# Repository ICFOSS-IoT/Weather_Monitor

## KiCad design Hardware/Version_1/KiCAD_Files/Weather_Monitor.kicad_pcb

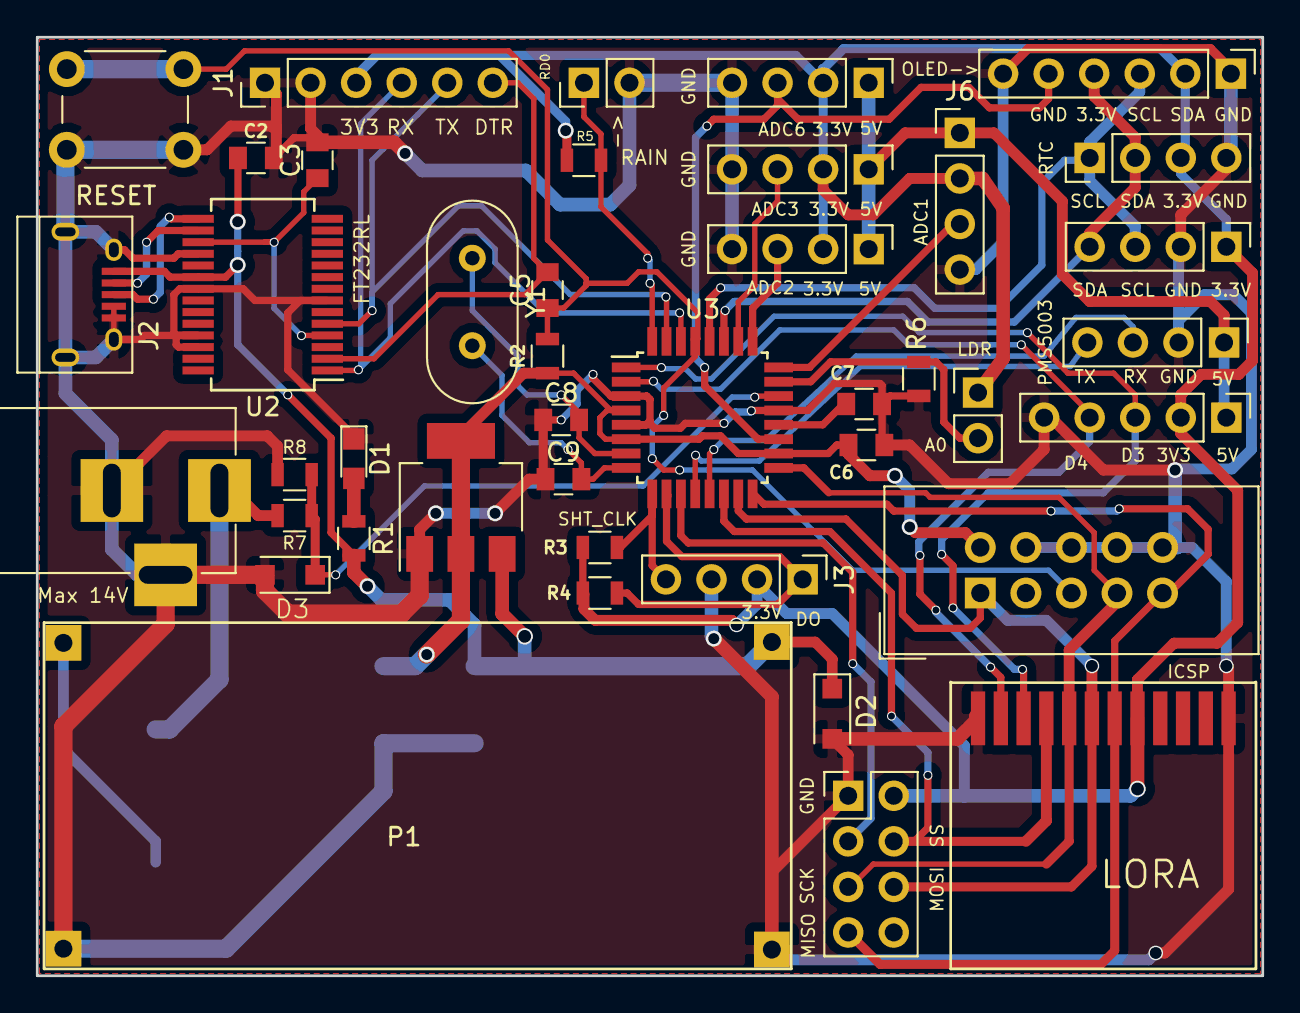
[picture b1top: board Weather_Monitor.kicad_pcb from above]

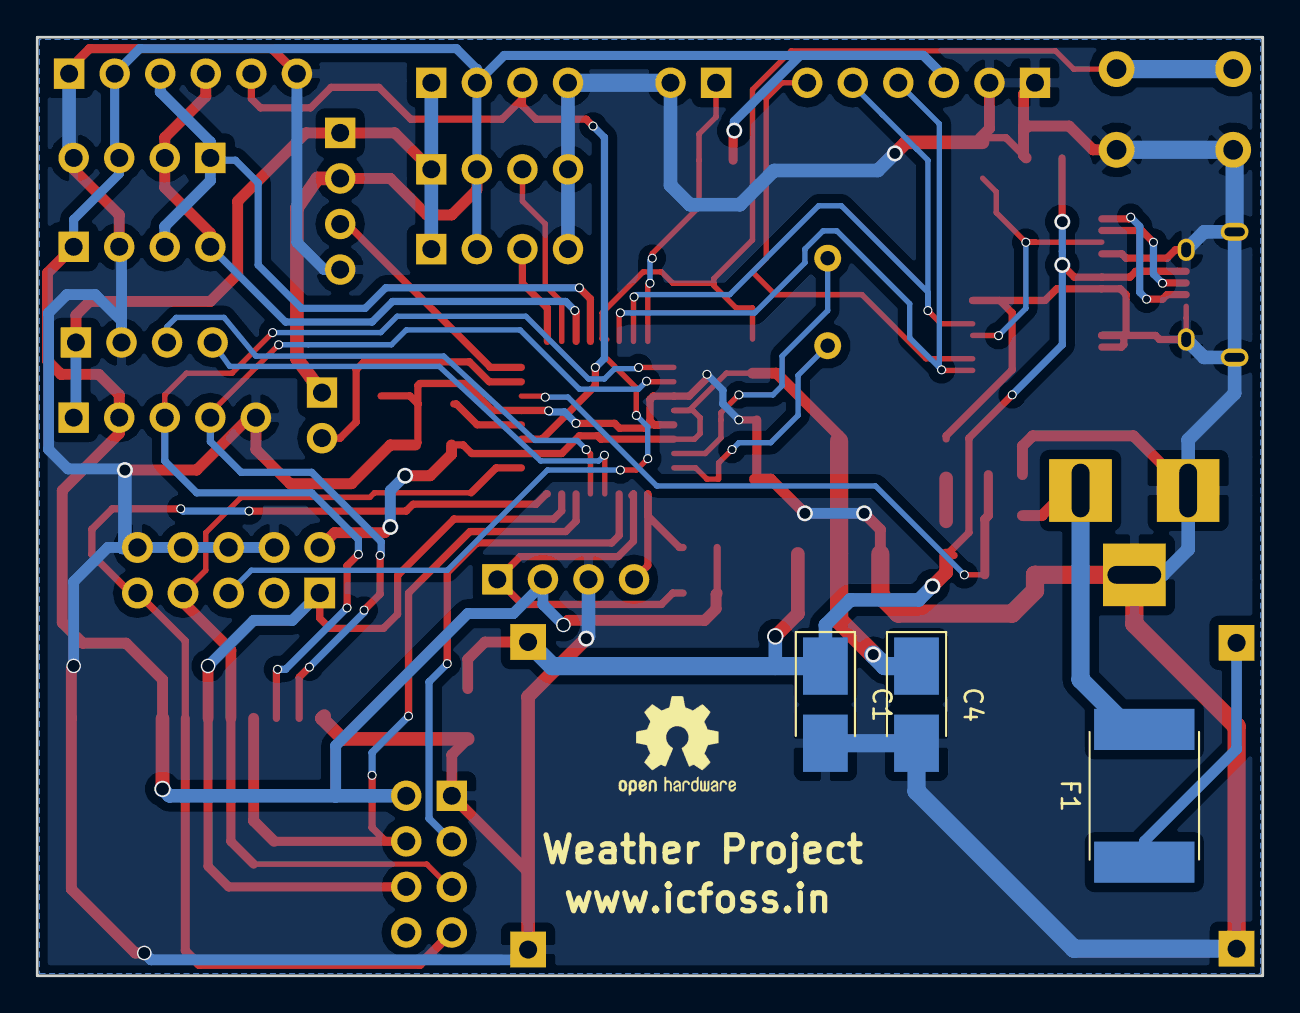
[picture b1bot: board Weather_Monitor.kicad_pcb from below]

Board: 2 copper layers, 68.3 x 52.3 mm, 45 parts (3 on the bottom side), 38 nets.

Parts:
C1, C4: 10uF; CP_Tantalum_Case-B_EIA-3528-21_Hand
C2, C3, C6, C7: 0.1uF; C_0805
C5: 0.1uf; C_0805
C8, C9: 22pF; C_0805
CON1: BARREL_JACK
CON2: AVR-ISP-10; IDC-Header_2x05_Pitch2.54mm_Straight
D1: LED; LED_0805
D2: 5.1V; D_SOD-123F
D3: 3.3V; D_SOD-123F
F1: Fuse; Fuse_SMD2920
J1: UART; Pin_Header_Straight_1x06_Pitch2.54mm
J2: MicroUSB; USB_Micro-B
J3: SHT11; Pin_Header_Straight_1x04_Pitch2.54mm
J4: RTC_DS3231; Pin_Header_Straight_1x04_Pitch2.54mm
J5: LoRa; XL_1278-SMT(SX1278)
J6: A1; Pin_Header_Straight_1x04_Pitch2.54mm
J7: A6; Pin_Header_Straight_1x04_Pitch2.54mm
J8: Rain_Sensor; Pin_Header_Straight_1x02_Pitch2.54mm
J9: BMP180; Pin_Header_Straight_1x04_Pitch2.54mm
J10: A2; Pin_Header_Straight_1x04_Pitch2.54mm
J13: NRF24L01; Pin_Header_Straight_2x04_Pitch2.54mm
J14: A3; Pin_Header_Straight_1x04_Pitch2.54mm
J16: PMS5003; Pin_Header_Straight_1x04_Pitch2.54mm
J17: LDR; Pin_Header_Straight_1x02_Pitch2.54mm
P1: LM2596
P2: OLED_I2C; Pin_Header_Straight_1x06_Pitch2.54mm
P3: Digital; Pin_Header_Straight_1x05_Pitch2.54mm
R1: 470E; R_0805
R2: 10K; R_0805
R3: 4.7k; R_0805
R4: 4.7K; R_0805
R5: 1K; R_0805
R6: 5K; R_0805
R7: 120K; R_0805
R8: 27K; R_0805
RESET: RESET; SW_PUSH_6mm
U1: AMS1117-3.3; SOT-223-3_TabPin2
U2: FT232RL; SSOP-28_5.3x10.2mm_Pitch0.65mm
U3: ATMEGA328P-AU; TQFP-32_7x7mm_Pitch0.8mm
Y1: 16MHz; Crystal_HC49-U_Vertical

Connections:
+3V3: C4.1, C7.1, CON2.2, R2.1, U1.2, U3.4, U3.6, U3.18
+5V: C1.1, C2.1, D2.1, J2.1, P1.2, R1.2, U1.3, U2.20
+BATT: CON1.1, F1.2, R7.1
/3.3V: J1.3, J3.2, J4.3, J5.5, J6.2, J7.2, J9.1, J10.2, J13.2, J14.2, J17.1, P2.2, P3.2, R3.1, R4.1, R5.1
/5V: J6.1, J7.1, J10.1, J14.1, J16.1, P3.1
/ADC1: J6.3, U3.24
/ADC2: J10.3, U3.25
/ADC3: J14.3, U3.26
/ADC6: J7.3, P2.5, U3.19
/ADC7: D3.1, R7.2, R8.1, U3.22
/D3: J5.10, P3.3, U3.1
/D4: J5.11, P3.4, U3.2
/DTR: C5.2, J1.6, U2.2
/LDR_A0: J17.2, R6.1, U3.23
/MISO: CON2.9, J5.6, J13.7, U3.16
/MOSI: CON2.1, J5.7, J13.6, U3.15
/PMS5003_Rx: J16.3, U3.13
/PMS5003_Tx: J16.4, U3.12
/RF_CE: J13.3, U3.11
/Rain_D0: J8.1, R5.2, U3.32
/Reset: C5.1, CON2.5, R2.2, RESET.1, U3.29
/Rx: J1.4, U2.1, U3.30
/SCK: CON2.7, J5.8, J13.5, U3.17
/SCL: J4.1, J9.3, P2.3, U3.28
/SDA: J4.2, J9.4, P2.4, U3.27
/SHT11_CLK: J3.4, R3.2, U3.9
/SHT11_D0: J3.1, R4.2, U3.10
/SS: J5.9, J13.4, U3.14
/Tx: J1.5, U2.5, U3.31
GND: C1.2, C2.2, C3.2, C4.2, C6.1, C7.2, C8.1, C9.1, CON1.2, CON1.3, CON2.4, CON2.6, CON2.8, CON2.10, D1.1, D2.2, D3.2, J1.1, J1.2, J2.4, J2.5, J2.6, J3.3, J4.4, J5.1, J5.12, J6.4, J7.4, J8.2, J9.2, J10.4, J13.1, J14.4, J16.2, P1.3, P1.4, P2.1, P2.6, P3.5, R6.2, R8.2, RESET.2, U1.1, U2.7, U2.18, U2.21, U2.25, U2.26, U3.3, U3.5, U3.21
unnamed: C3.1, U2.4, U2.17
unnamed: C6.2, U3.20
unnamed: C8.2, U3.7, Y1.1
unnamed: C9.2, U3.8, Y1.2
unnamed: D1.2, R1.1
unnamed: F1.1, P1.1
unnamed: J2.2, U2.16
unnamed: J2.3, U2.15

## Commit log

2017-11-15 Gerber and Libs
2017-11-29 Schematic-PDF
